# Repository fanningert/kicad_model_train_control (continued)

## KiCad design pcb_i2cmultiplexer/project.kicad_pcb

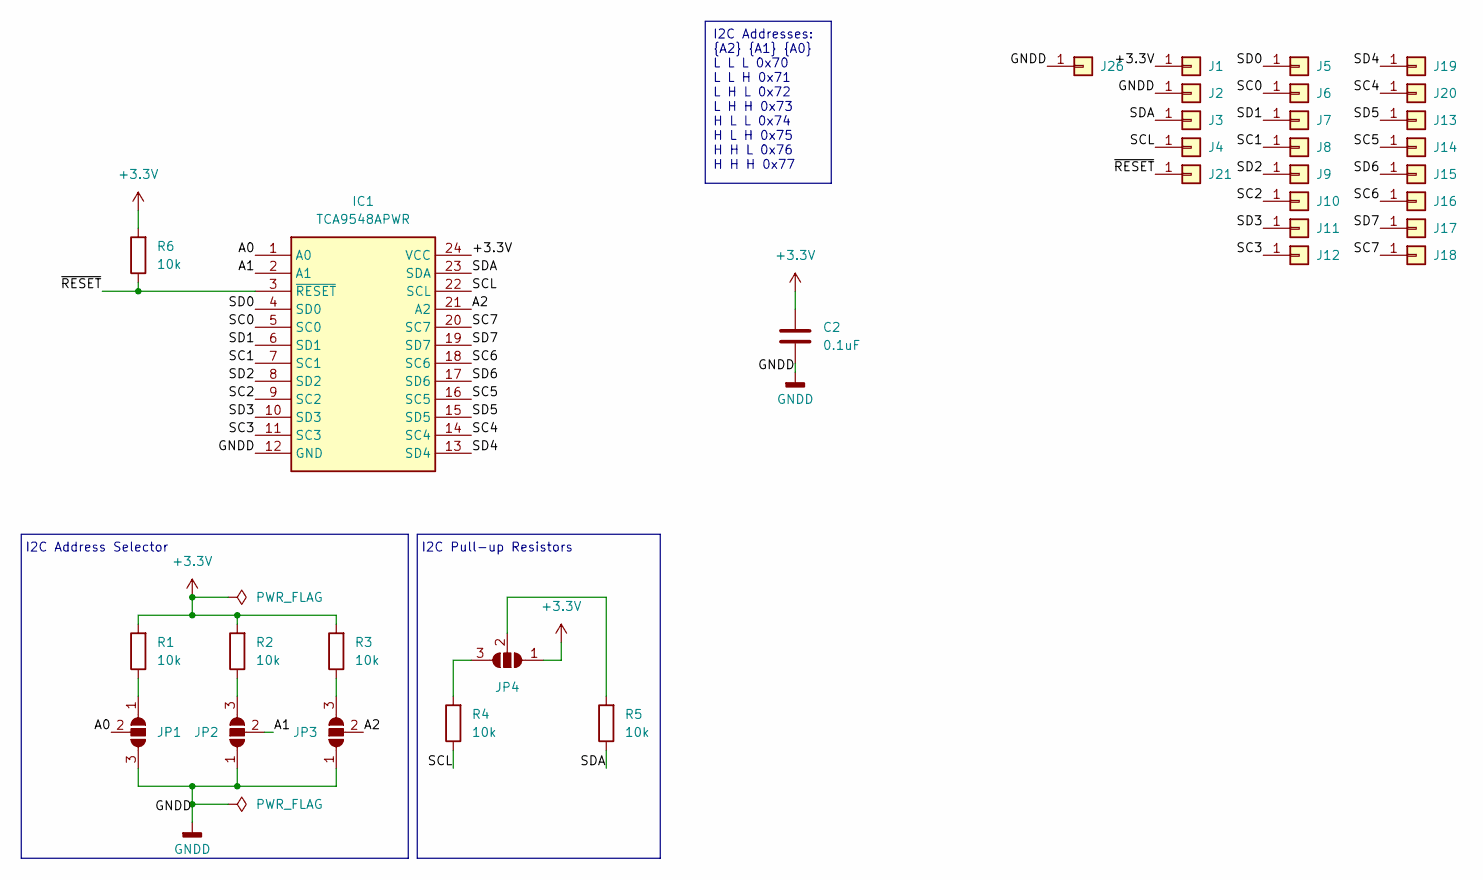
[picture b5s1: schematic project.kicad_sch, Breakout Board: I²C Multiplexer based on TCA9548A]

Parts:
C2: 0.1uF; C_0402_1005Metric_Pad0.74x0.62mm_HandSolder
IC1: TCA9548APWR; SOP65P640X120-24N; Mouser Part Number 595-TCA9548APWR
J1, J2, J3, J4, J5, J6, J7, J8, J9, J10, J11, J12, J13, J14, J15, J16, J17, J18, J19, J20, J21, J26: Castellated_Hole02
JP1, JP2, JP3, JP4: SolderJumper_3_Open; SolderJumper-3_P1.3mm_Open_RoundedPad1.0x1.5mm
R1, R2, R3, R4, R5, R6: 10k; R_0402_1005Metric_Pad0.72x0.64mm_HandSolder

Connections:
+3.3V: C2.1, IC1.24 (VCC), J1.1, JP4.1 (A), R1.2, R2.2, R3.2, R6.2
/A0: IC1.1 (A0), JP1.2 (C)
/A1: IC1.2 (A1), JP2.2 (C)
/A2: IC1.21 (A2), JP3.2 (C)
/SC0: IC1.5 (SC0), J6.1
/SC1: IC1.7 (SC1), J8.1
/SC2: IC1.9 (SC2), J10.1
/SC3: IC1.11 (SC3), J12.1
/SC4: IC1.14 (SC4), J20.1
/SC5: IC1.16 (SC5), J14.1
/SC6: IC1.18 (SC6), J16.1
/SC7: IC1.20 (SC7), J18.1
/SCL: IC1.22 (SCL), J4.1, R4.1
/SD0: IC1.4 (SD0), J5.1
/SD1: IC1.6 (SD1), J7.1
/SD2: IC1.8 (SD2), J9.1
/SD3: IC1.10 (SD3), J11.1
/SD4: IC1.13 (SD4), J19.1
/SD5: IC1.15 (SD5), J13.1
/SD6: IC1.17 (SD6), J15.1
/SD7: IC1.19 (SD7), J17.1
/SDA: IC1.23 (SDA), J3.1, R5.1
/~RESET: IC1.3 (~RESET), J21.1, R6.1
GNDD: C2.2, IC1.12 (GND), J2.1, J26.1, JP1.3 (B), JP2.1 (A), JP3.1 (A)
unnamed: JP1.1 (A), R1.1
unnamed: JP2.3 (B), R2.1
unnamed: JP3.3 (B), R3.1
unnamed: JP4.3 (B), R4.2
unnamed: JP4.2 (C), R5.2

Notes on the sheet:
I2C Addresses: {A2} {A1} {A0} L L L 0x70 L L H 0x71 L H L 0x72 L H H 0x73 H L L 0x74 H L H 0x75 H H L 0x76 H H H 0x77
I2C Pull-up Resistors
I2C Address Selector

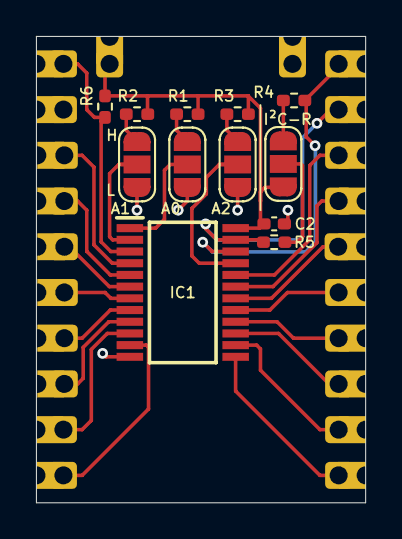
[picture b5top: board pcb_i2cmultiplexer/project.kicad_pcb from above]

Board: 2 copper layers, 18.3 x 25.9 mm, 35 parts (1 on the bottom side), 29 nets.

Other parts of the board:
QR*****: https://github.com/fanningert/kicad_pcb_i2cmultip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; //github.com/fanningert/kicad_pcb_i2cmultiplexer

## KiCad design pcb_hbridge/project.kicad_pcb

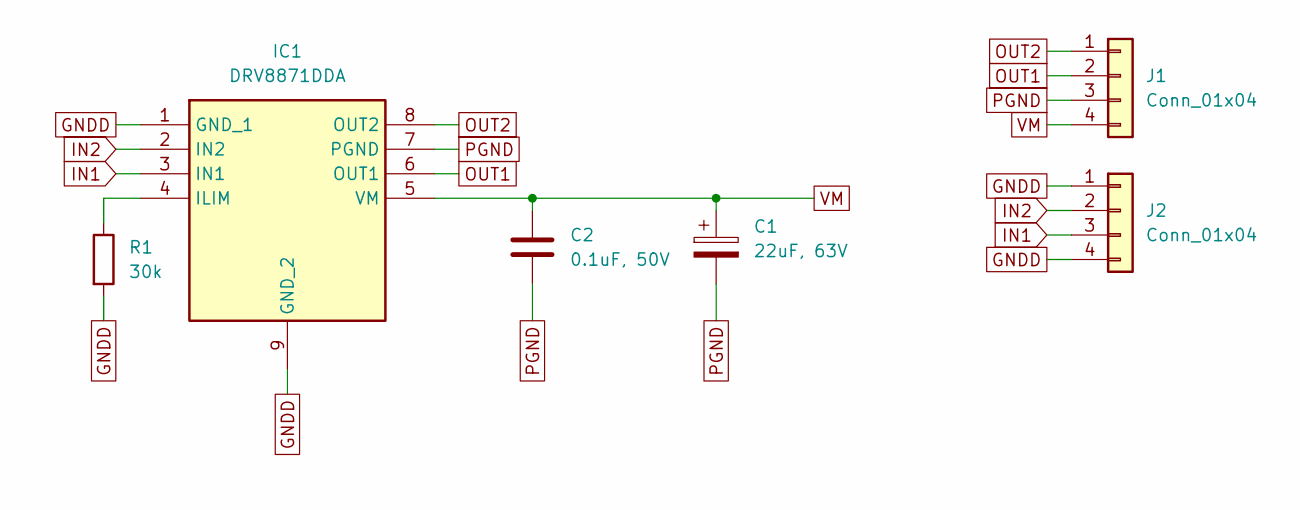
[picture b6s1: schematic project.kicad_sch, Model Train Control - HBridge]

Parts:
C1: 22uF, 63V; CP_Elec_6.3x7.7; Manufacturer_Part_Number Capacitor, 22.0uF, 63V, D6.3xL7.7 SMD; JLCPCB# C473196
C2: 0.1uF, 50V; C_0805_2012Metric_Pad1.18x1.45mm_HandSolder; Manufacturer_Part_Number Capacitor, 0.1uF, 50V, 0805 SMD; JLCPCB# C49678
IC1: DRV8871DDA; SOIC127P600X170-9N; Manufacturer_Part_Number DRV8871DDA; JLCPCB# C1556867
J1, J2: Conn_01x04; PinHeader_1x04_P2.54mm_Vertical
R1: 30k; R_1206_3216Metric_Pad1.30x1.75mm_HandSolder; Manufacturer_Part_Number Resistor, 30.0kΩ, 1206 SMD; JLCPCB# C319666

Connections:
GNDD: IC1.1 (GND_1), IC1.9 (GND_2), J2.1, J2.4, R1.2
IN1: IC1.3 (IN1), J2.3
IN2: IC1.2 (IN2), J2.2
unnamed: IC1.4 (ILIM), R1.1
OUT1: IC1.6 (OUT1), J1.2
OUT2: IC1.8 (OUT2), J1.1
PGND: C1.2, C2.2, IC1.7 (PGND), J1.3
VM: C1.1, C2.1, IC1.5 (VM), J1.4

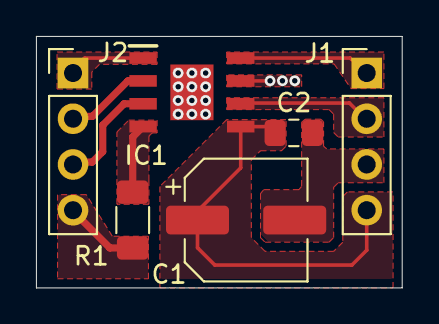
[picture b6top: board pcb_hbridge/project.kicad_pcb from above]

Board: 2 copper layers, 20.3 x 14.0 mm, 6 parts (0 on the bottom side), 8 nets.

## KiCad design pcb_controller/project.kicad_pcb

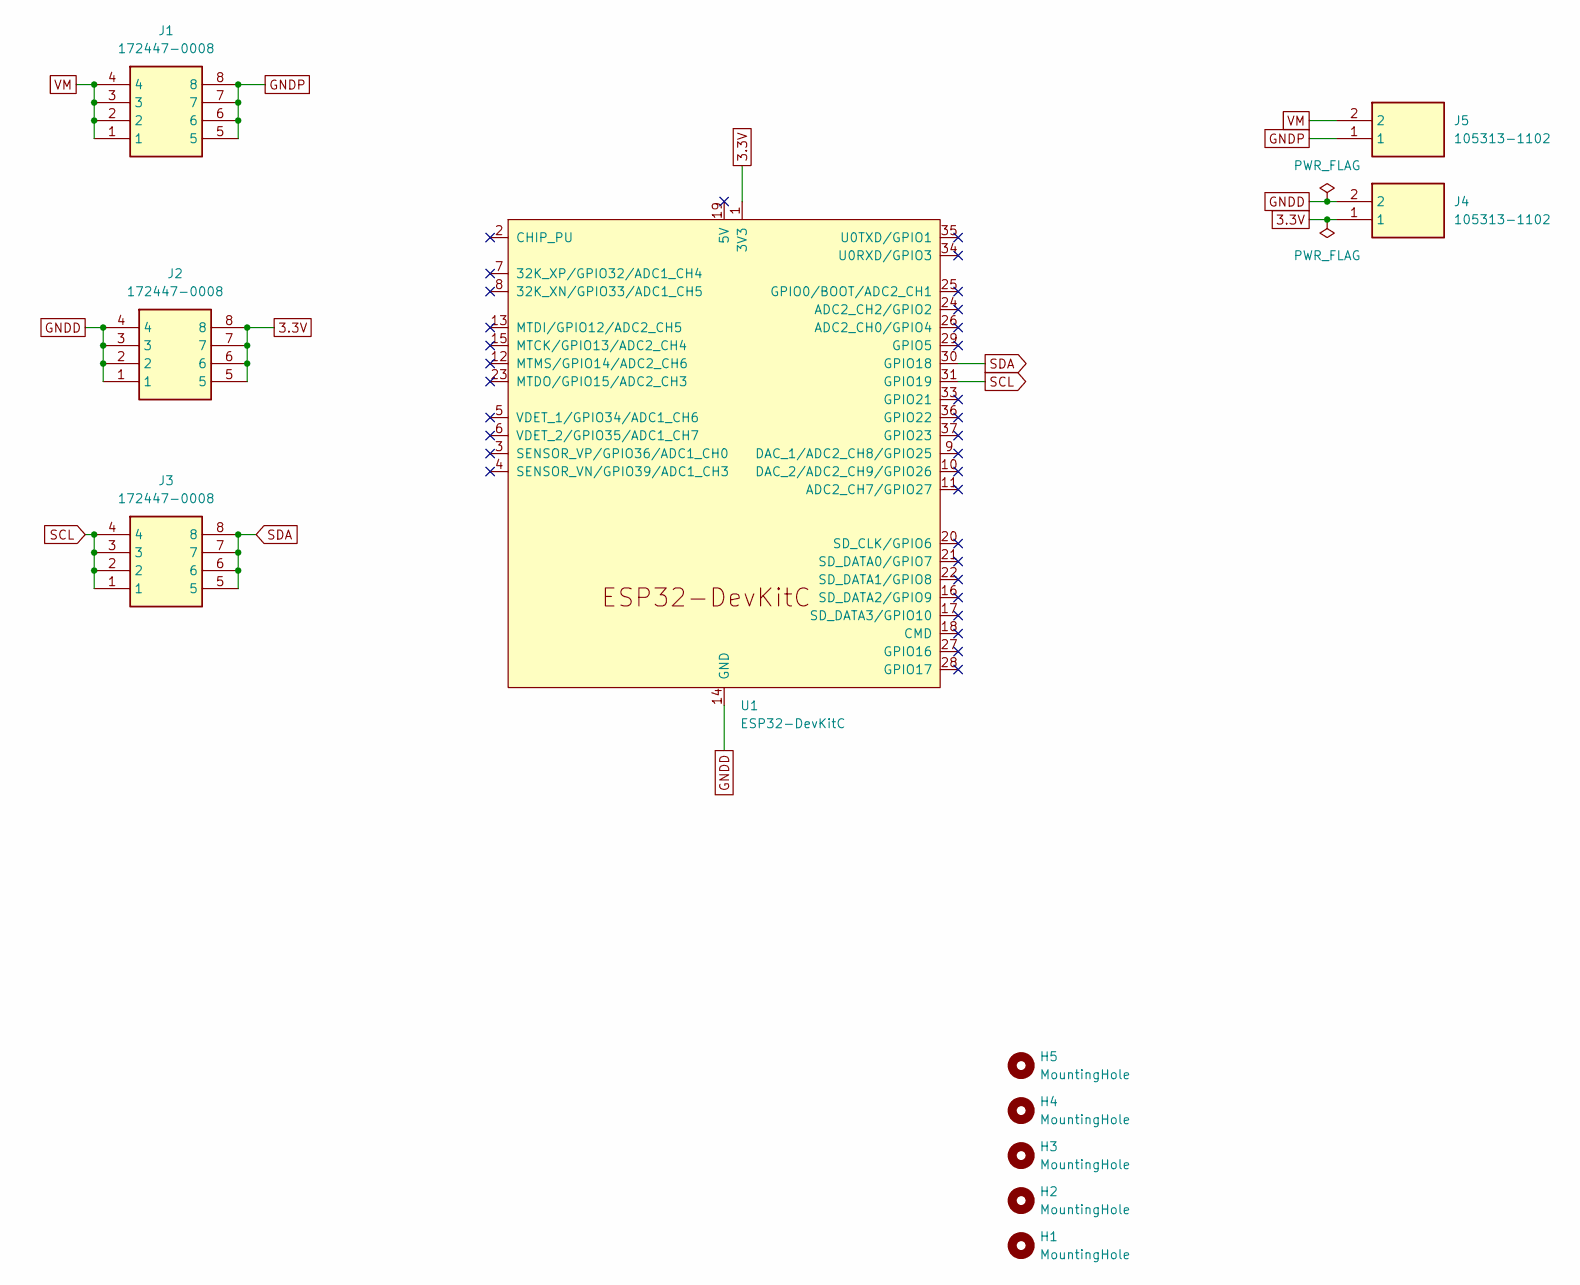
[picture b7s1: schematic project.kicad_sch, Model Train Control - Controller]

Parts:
H1, H2, H3, H4, H5: MountingHole; MountingHole_3.2mm_M3_Pad_Via
J1, J2, J3: 172447-0008; 172447-YY08; Manufacturer_Part_Number 172447-0008; Mouser# 538-172447-0008
J4, J5: 105313-1102; 1053131102; Manufacturer_Part_Number 105313-1102; Mouser# 538-105313-1102
U1: ESP32-DevKitC

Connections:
3.3V: J2.5, J2.6, J2.7, J2.8, J4.1, U1.1 (3V3)
GNDD: J2.1, J2.2, J2.3, J2.4, J4.2, U1.14 (GND), U1.32 (GND), U1.38 (GND)
GNDP: J1.5, J1.6, J1.7, J1.8, J5.1
SCL: J3.1, J3.2, J3.3, J3.4, U1.31 (GPIO19)
SDA: J3.5, J3.6, J3.7, J3.8, U1.30 (GPIO18)
VM: J1.1, J1.2, J1.3, J1.4, J5.2

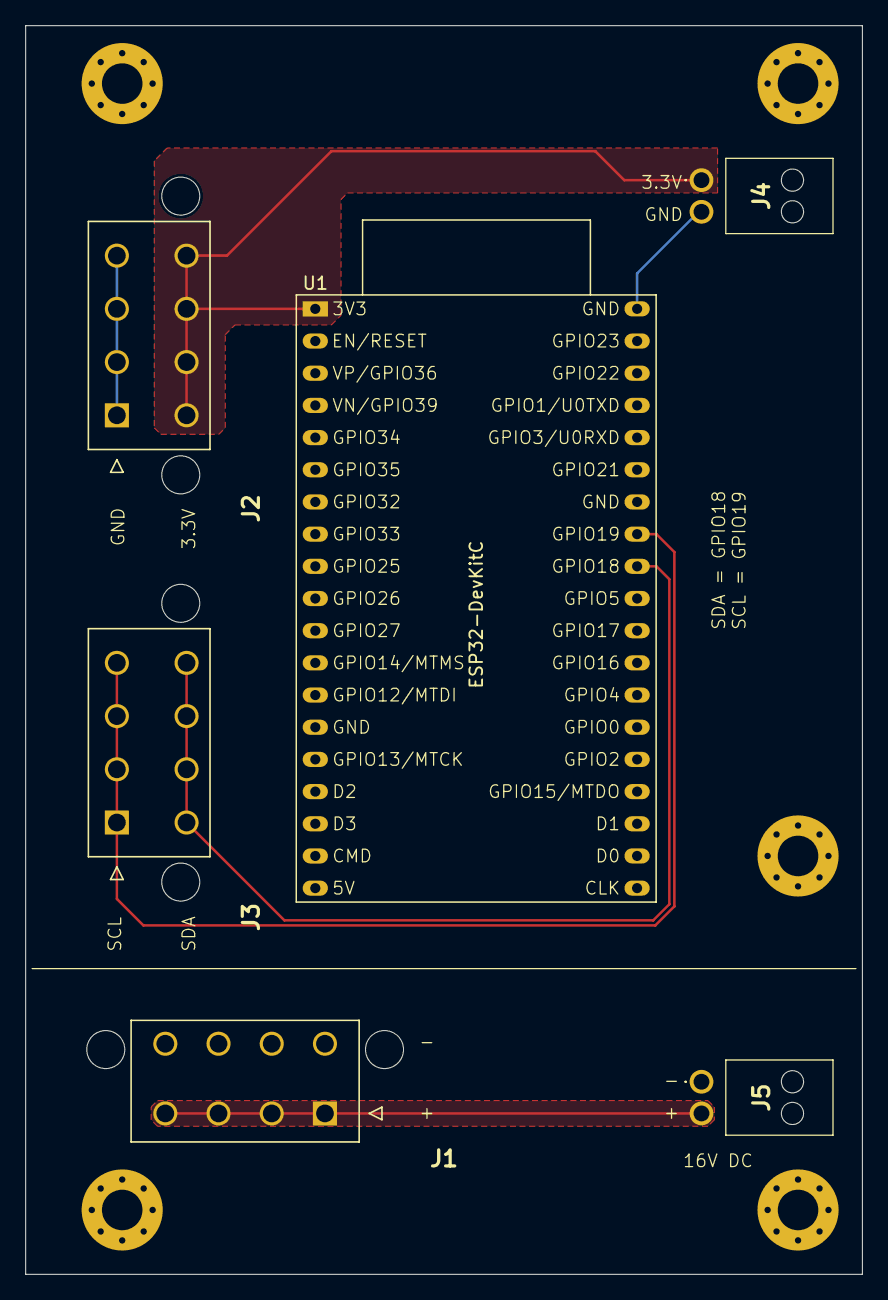
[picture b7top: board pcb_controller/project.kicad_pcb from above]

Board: 2 copper layers, 66.0 x 98.6 mm, 11 parts (0 on the bottom side), 6 nets.

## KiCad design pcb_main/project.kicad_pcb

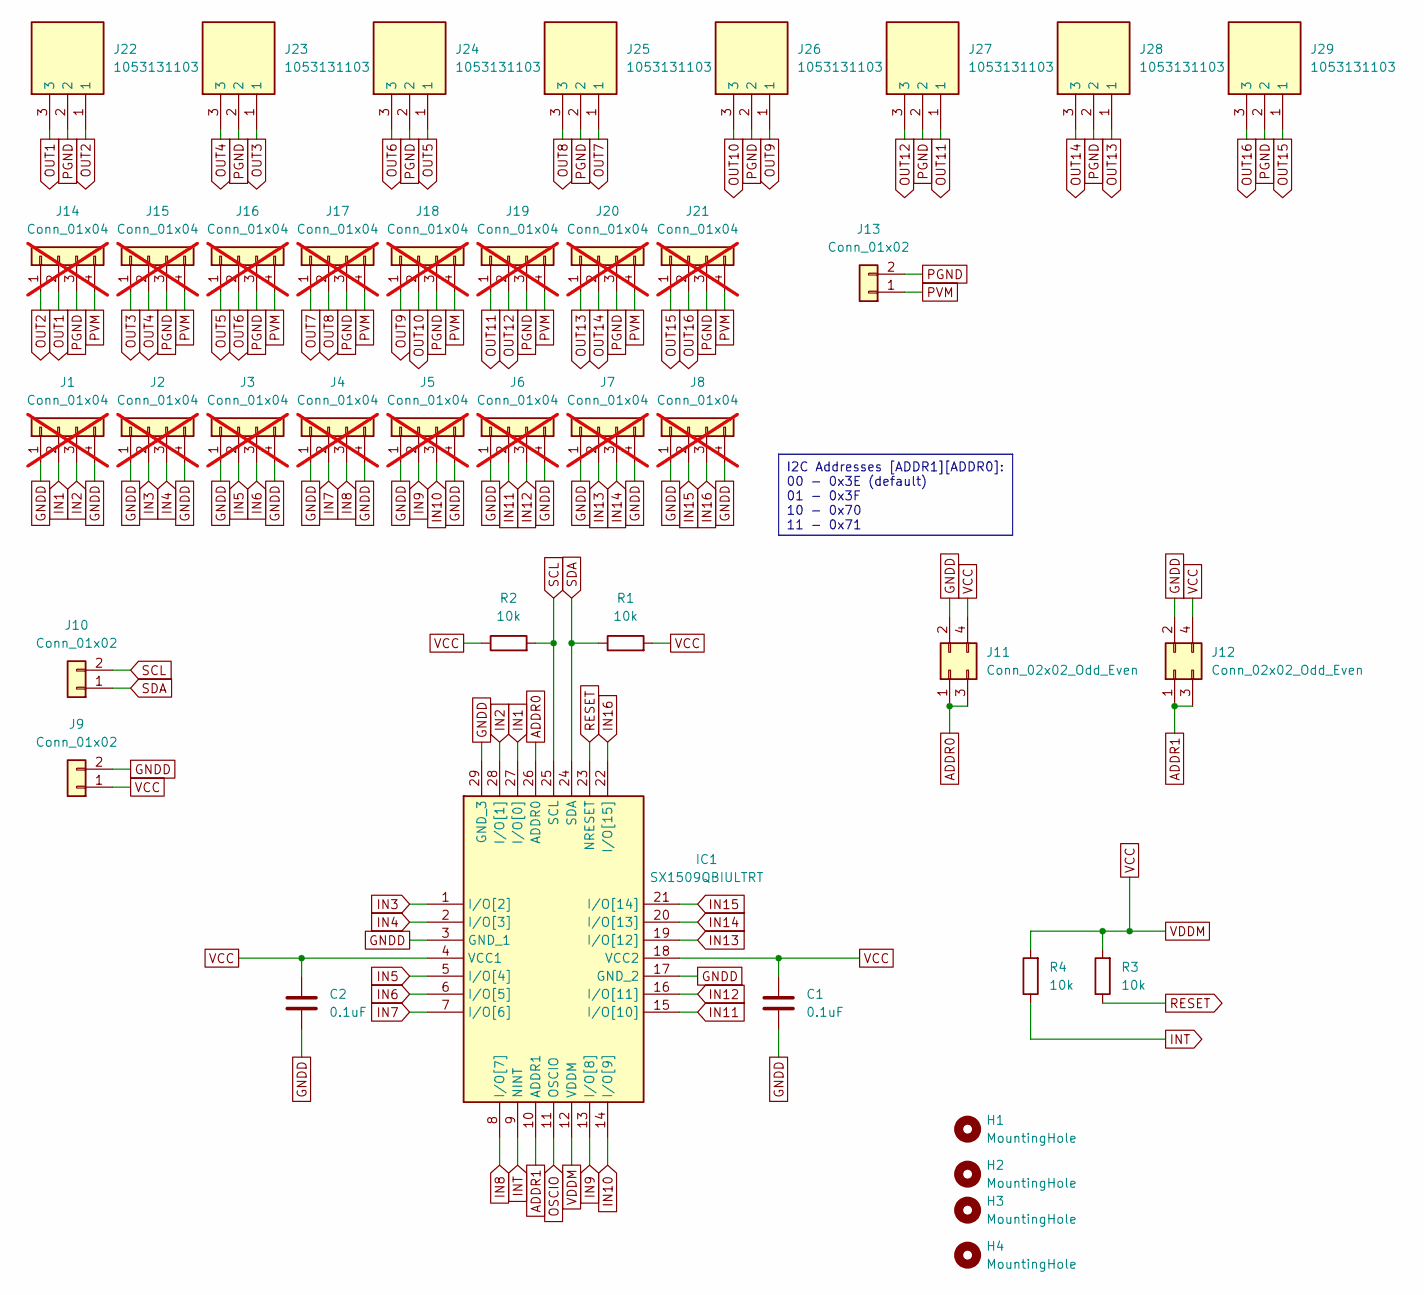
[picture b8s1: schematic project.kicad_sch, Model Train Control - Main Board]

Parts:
C1, C2: 0.1uF; C_0402_1005Metric; Manufacturer_Part_Number Capacitor, 0.1uF, 50V, 0402 SMD; JLCPCB# C110251
H1, H2, H3, H4: MountingHole; MountingHole_3.2mm_M3_Pad_Via
IC1: SX1509QBIULTRT; QFN40P400X400X60-29N-D; Manufacturer_Part_Number SX1509QBIULTRT; JLCPCB# C2652294
J1, J2, J3, J4, J5, J6, J7, J8, J14, J15, J16, J17, J18, J19, J20, J21: Conn_01x04; PinHeader_1x04_P2.54mm_Vertical; not fitted
J9, J10, J13: Conn_01x02; PinHeader_1x02_P2.54mm_Vertical; JLCPCB# C492401
J11, J12: Conn_02x02_Odd_Even; PinHeader_2x02_P2.54mm_Vertical; JLCPCB# C492419
J22, J23, J24, J25, J26, J27, J28, J29: 1053131103; 105313YY03; Manufacturer_Part_Number 1053131103; Mouser# 538-105313-1103
R1, R2, R3, R4: 10k; R_0402_1005Metric; Manufacturer_Part_Number Resistor, 10.0kΩ, 0402 SMD; JLCPCB# C60490

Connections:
ADDR0: IC1.26 (ADDR0), J11.1, J11.3
ADDR1: IC1.10 (ADDR1), J12.1, J12.3
GNDD: C1.2, C2.2, IC1.3 (GND_1), IC1.17 (GND_2), IC1.29 (GND_3), J1.1, J1.4, J2.1, J2.4, J3.1, J3.4, J4.1, J4.4, J5.1, J5.4, J6.1, J6.4, J7.1, J7.4, J8.1, J8.4, J9.2, J11.2, J12.2
IN1: IC1.27 (I/O[0]), J1.2
IN2: IC1.28 (I/O[1]), J1.3
IN3: IC1.1 (I/O[2]), J2.2
IN4: IC1.2 (I/O[3]), J2.3
IN5: IC1.5 (I/O[4]), J3.2
IN6: IC1.6 (I/O[5]), J3.3
IN7: IC1.7 (I/O[6]), J4.2
IN8: IC1.8 (I/O[7]), J4.3
IN9: IC1.13 (I/O[8]), J5.2
IN10: IC1.14 (I/O[9]), J5.3
IN11: IC1.15 (I/O[10]), J6.2
IN12: IC1.16 (I/O[11]), J6.3
IN13: IC1.19 (I/O[12]), J7.2
IN14: IC1.20 (I/O[13]), J7.3
IN15: IC1.21 (I/O[14]), J8.2
IN16: IC1.22 (I/O[15]), J8.3
INT: IC1.9 (NINT), R4.1
OSCIO: IC1.11 (OSCIO)
OUT1: J14.2, J22.3
OUT2: J14.1, J22.1
OUT3: J15.1, J23.1
OUT4: J15.2, J23.3
OUT5: J16.1, J24.1
OUT6: J16.2, J24.3
OUT7: J17.1, J25.1
OUT8: J17.2, J25.3
OUT9: J18.1, J26.1
OUT10: J18.2, J26.3
OUT11: J19.1, J27.1
OUT12: J19.2, J27.3
OUT13: J20.1, J28.1
OUT14: J20.2, J28.3
OUT15: J21.1, J29.1
OUT16: J21.2, J29.3
PGND: J13.2, J14.3, J15.3, J16.3, J17.3, J18.3, J19.3, J20.3, J21.3, J22.2, J23.2, J24.2, J25.2, J26.2, J27.2, J28.2, J29.2
PVM: J13.1, J14.4, J15.4, J16.4, J17.4, J18.4, J19.4, J20.4, J21.4
RESET: IC1.23 (NRESET), R3.1
SCL: IC1.25 (SCL), J10.2, R2.2
SDA: IC1.24 (SDA), J10.1, R1.1
VCC: C1.1, C2.1, IC1.4 (VCC1), IC1.12 (VDDM), IC1.18 (VCC2), J9.1, J11.4, J12.4, R1.2, R2.1, R3.2, R4.2

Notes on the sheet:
I2C Addresses [ADDR1][ADDR0]: 00 - 0x3E (default) 01 - 0x3F 10 - 0x70 11 - 0x71

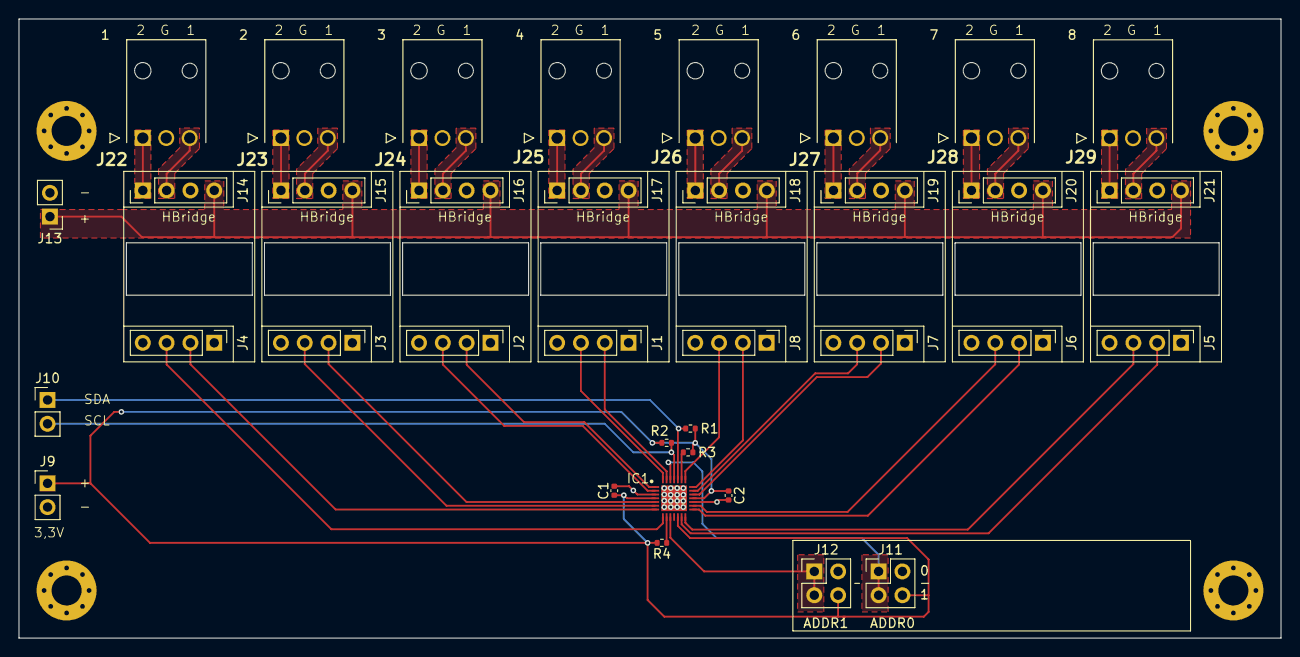
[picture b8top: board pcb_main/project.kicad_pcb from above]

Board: 2 copper layers, 134.6 x 66.0 mm, 40 parts (0 on the bottom side), 42 nets.

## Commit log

2024-04-01 Initial version, migrate from internal gitea repository to github
2024-04-01 Correct workflow names and upload action
2024-04-01 correct bom columns
2024-04-01 Correct JLCPCB# to LCSC# in BOM
2024-04-01 Update test workflow action upload-artifact from v3 to v4
2024-04-01 Optimize workflow
2024-04-01 Correct workflow error with asset upload
2024-04-01 Correct workflow error with upload release asset
2024-04-01 Little Update on REAMDE-md
2024-04-01 Add ESPHome example
2024-04-01 Change test kibot workflow for only changes of speific directories
2024-05-04 Change Multi-Board to Single-Board design
2024-05-04 Add missing netclass and close open connections
2024-05-04 Add missing PWR_FLAGs
2024-05-04 Correct BOM values
2024-05-04 Correct ERC errors
2024-05-04 Correct BOM errors
2024-05-04 Correct description field warnings
2024-05-04 Correct ECR Warnings
2024-05-04 Harmonize package sizing of components
2024-05-04 Update workflow
2024-05-04 Add badge
2024-05-04 Correct badge in README
2024-05-04 Update I²C addresses
2024-05-04 Update README and workflow
2024-05-04 Little style change
2024-05-04 Update BOM
2024-05-05 Update pcb layout
2024-05-05 Add Kiri output, correct some output errors
2024-05-05 correct R16 value
2024-05-05 correct kiri parameter error
2024-05-09 Update pcb, bom and add 3D view
2024-05-09 Update kiri config and 3D export
2024-05-09 Change check workflow to every push
2024-05-09 change Kiri config
2024-05-09 disable kiri
2024-05-09 Change size of 3d
2024-05-09 Add blender render
2024-05-09 Add variants for Master and Slave
2024-05-09 Update variant config
2024-05-09 Convert 'config' to 'Config'
2024-05-09 Update workflow and variant config
2024-05-09 Correct error with variant MasterESP32Devkit
2024-05-09 Change retention for DRC and ERC result to 1 day
2024-05-09 Change from run_erc and run_drc to erc and drc
2024-05-09 Disable blender render
2024-05-09 Add missing variant config in production
2024-05-09 Correct variant setting for components
2024-05-09 Move location of power line led and set LCSC-IDs
2024-05-09 Change master,slave to primary and sub node
2024-05-09 Correct markdown error in README
2024-05-09 Correct type in README
2024-05-09 Change workflow, to execute only on kibot config or pcb changes
2024-05-10 Add LED for 3.3V power line
2024-05-11 Change to I4214DDY-T1-GE3 and update PCB
2024-05-11 Correct schematic symbol for Current Regulator Diodes, Update Kibot config
2024-05-11 Correct kitbot config
2024-05-11 Update images
2024-05-11 Optimize PCB
2024-05-11 Optimize PCB to reduce vias
2024-05-12 Add AISLER bom support and assigned components
2024-05-23 Update BOM Mouser
2024-06-16 New package version of model train controller
2024-06-16 Remove 3D for panelized PCB
2024-06-16 Add Panelize connector to PCB_Core
2024-06-16 Optimize cutout rounding
2024-06-17 Add ESP32Dev PCB
2024-06-17 Correct ESP32Dev PCB panelize
2024-07-04 Change ioexpander pcb
2024-07-04 change mouse bites sizes
2025-02-08 TRy to change badge absolute path to relative path
2025-02-08 Another Try to change to relative path
2025-02-08 Removed badge
